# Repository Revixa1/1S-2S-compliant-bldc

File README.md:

# 1S-2S-compliant-bldc
BLDC(Brush Less DC)/PMSM(permanent magnet synchronous motor) motor supplied by 1 to 2S battery with compliance capabilities

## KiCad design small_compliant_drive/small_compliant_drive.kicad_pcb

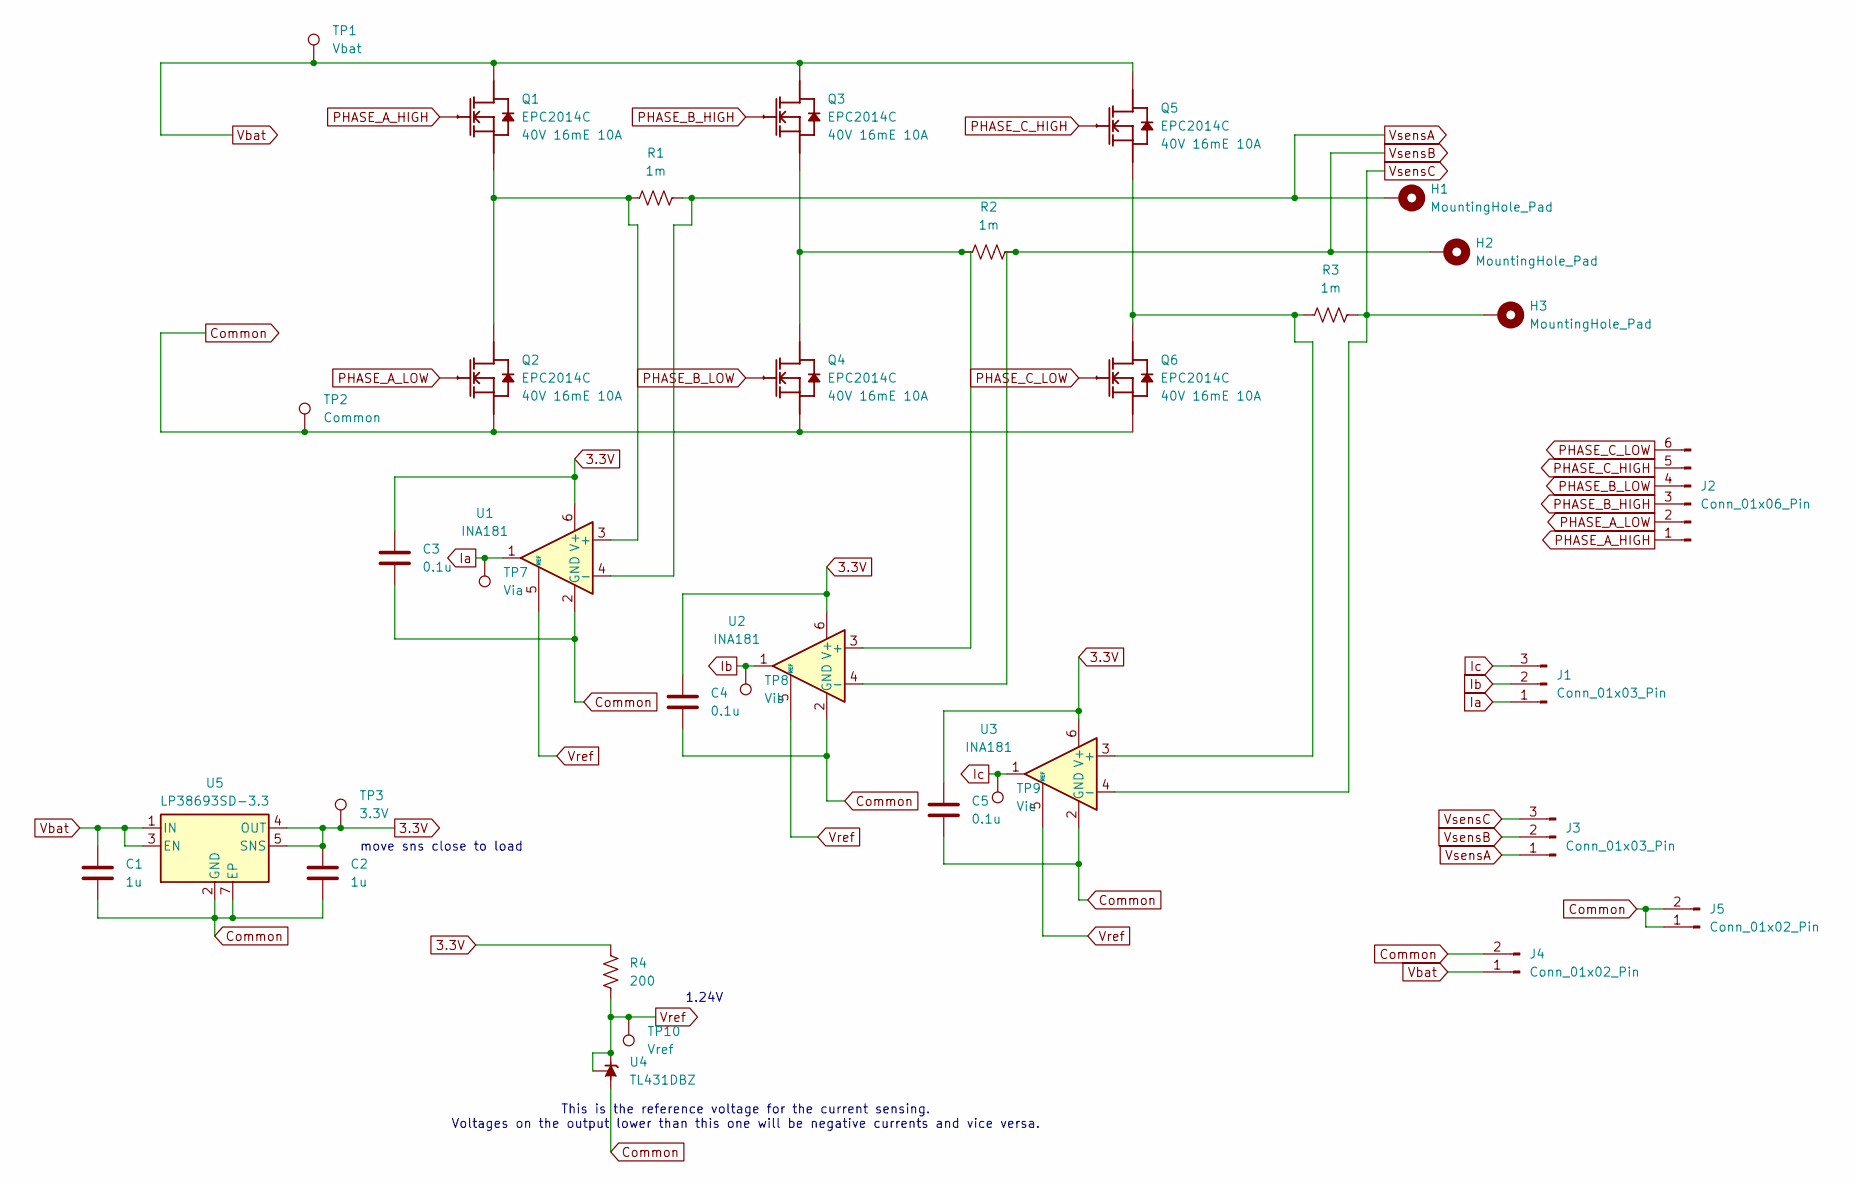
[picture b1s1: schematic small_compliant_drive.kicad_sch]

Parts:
C1, C2: 1u; C_0603_1608Metric
C3, C4, C5: 0.1u; C_0603_1608Metric
H1, H2, H3: MountingHole_Pad; MountingHole_3mm_Pad
J1, J3: Conn_01x03_Pin; PinSocket_1x03_P2.54mm_Vertical
J2: Conn_01x06_Pin; PinHeader_1x06_P2.54mm_Vertical
J4: Conn_01x02_Pin; AMASS_XT30U-M_1x02_P5.0mm_Vertical
J5: Conn_01x02_Pin; PinHeader_1x02_P2.54mm_Vertical
Q1, Q2, Q3, Q4, Q5, Q6: EPC2014C; D0199
R1, R2, R3: 1m; R_2512_6332Metric
R4: 200; R_0603_1608Metric
TP1: Vbat; TestPoint_Pad_D2.0mm
TP2: Common; TestPoint_Pad_D2.0mm
TP3: 3.3V; TestPoint_Pad_D2.0mm
TP7: Via; TestPoint_Pad_D2.0mm
TP8: Vib; TestPoint_Pad_D2.0mm
TP9: Vic; TestPoint_Pad_D2.0mm
TP10: Vref; TestPoint_Pad_D2.0mm
U1, U2, U3: INA181; SOT-23-6
U4: TL431DBZ; SOT-23
U5: LP38693SD-3.3; WSON-6-1EP_3x3mm_P0.95mm

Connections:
3.3V: C2.1, C3.1, C4.1, C5.1, R4.2, TP3.1, U1.6 (V+), U2.6 (V+), U3.6 (V+), U5.4 (OUT), U5.5 (SNS)
Common: C1.2, C2.2, C3.2, C4.2, C5.2, J4.2, J5.1, J5.2, Q2.2 (Sub), Q2.4 (S1), Q4.2 (Sub), Q4.4 (S1), Q6.2 (Sub), Q6.4 (S1), TP2.1, U1.2 (GND), U2.2 (GND), U3.2 (GND), U4.3 (A), U5.2 (GND), U5.7 (EP); also elsewhere on the board
Ia: J1.1, TP7.1, U1.1
Ib: J1.2, TP8.1, U2.1
Ic: J1.3, TP9.1, U3.1
unnamed: Q1.2 (Sub), Q1.4 (S1), Q2.3 (D1), Q2.5 (D2), R1.1, U1.3 (+)
unnamed: Q3.2 (Sub), Q3.4 (S1), Q4.3 (D1), Q4.5 (D2), R2.1, U2.3 (+)
unnamed: Q5.2 (Sub), Q5.4 (S1), Q6.3 (D1), Q6.5 (D2), R3.1, U3.3 (+)
PHASE_A_HIGH: J2.1, Q1.1 (G)
PHASE_A_LOW: J2.2, Q2.1 (G)
PHASE_B_HIGH: J2.3, Q3.1 (G)
PHASE_B_LOW: J2.4, Q4.1 (G)
PHASE_C_HIGH: J2.5, Q5.1 (G)
PHASE_C_LOW: J2.6, Q6.1 (G)
Vbat: C1.1, J4.1, Q1.3 (D1), Q1.5 (D2), Q3.3 (D1), Q3.5 (D2), Q5.3 (D1), Q5.5 (D2), TP1.1, U5.1 (IN), U5.3 (EN), U5.6 (IN); also elsewhere on the board
Vref: R4.1, TP10.1, U1.5 (REF), U2.5 (REF), U3.5 (REF), U4.1 (K), U4.2 (REF)
VsensA: H1.1, J3.1, R1.2, U1.4 (-)
VsensB: H2.1, J3.2, R2.2, U2.4 (-)
VsensC: H3.1, J3.3, R3.2, U3.4 (-)

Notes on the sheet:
1.24V
move sns close to load
This is the reference voltage for the current sensing. Voltages on the output lower than this one will be negative currents and vice versa.

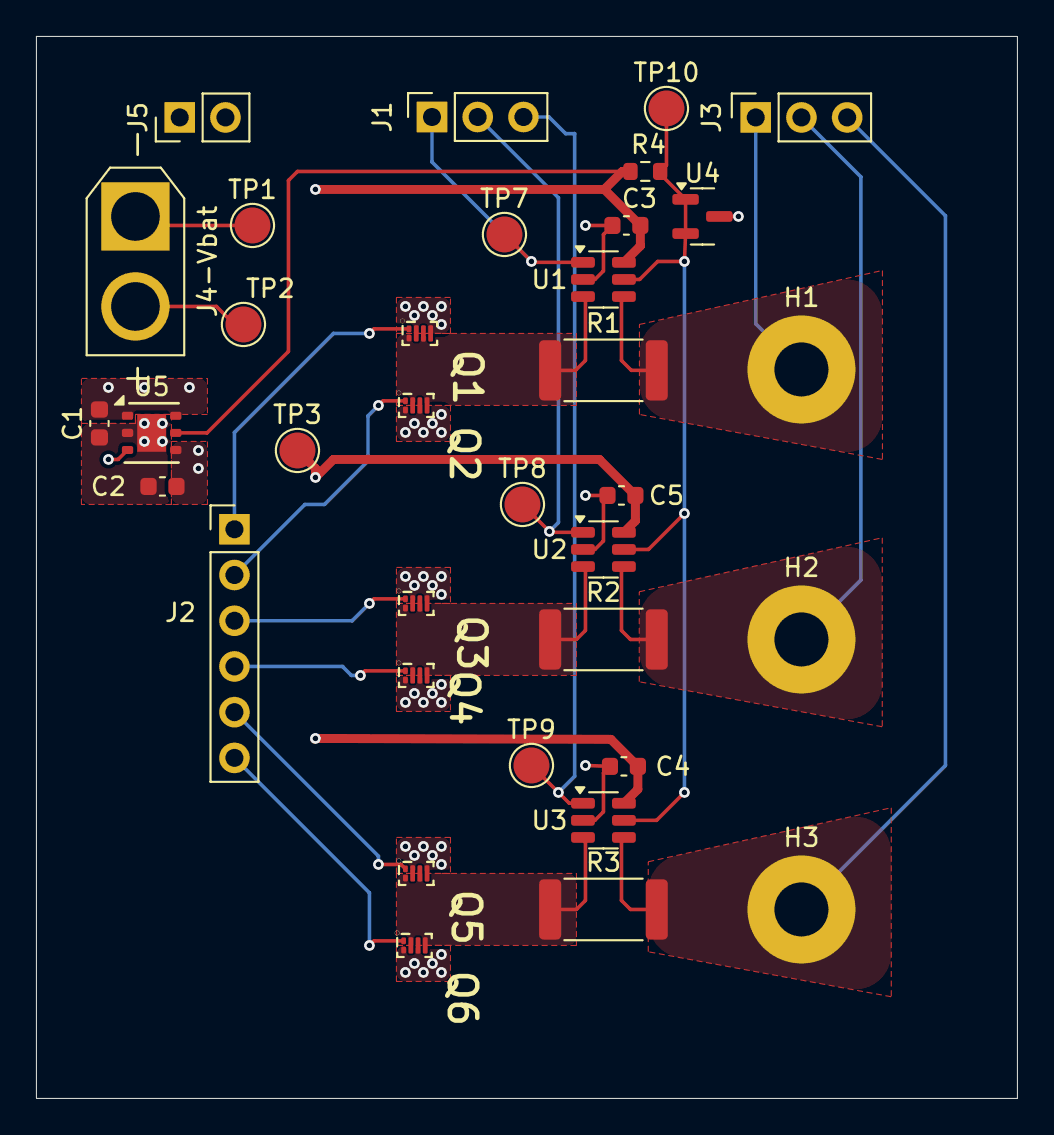
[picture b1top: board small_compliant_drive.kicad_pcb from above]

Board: 4 copper layers, 54.5 x 59.0 mm, 35 parts (0 on the bottom side), 19 nets.

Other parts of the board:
J4-Vbat: Conn_01x02_Pin; AMASS_XT30U-M_1x02_P5.0mm_Vertical

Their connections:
Common: J4-Vbat.2; also elsewhere on the board
Vbat: J4-Vbat.1; also elsewhere on the board

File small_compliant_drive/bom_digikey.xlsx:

'Reference' | 'Value' | 'Datasheet' | 'Footprint' | 'Qty' | 'DNP' | Price | Qty Factor | subTotal | qtyTotal |  | Links
'C1,C2' | '1u' | '~' | 'Capacitor_SMD:C_0603_1608Metric' | 2 | '' | 0.24099999999999999 | 10 | 4.82 | 20 |  | https://www.digikey.ca/en/products/detail/taiyo-yuden/UMK107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
'C3,C4,C5' | '0.1u' | '~' | 'Capacitor_SMD:C_0603_1608Metric' | 3 | '' | 2.12E-2 | 16.7 | 1.06212 | 50 |  | https://www.digikey.ca/en/products/detail/samsung-electro-me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
'J1,J3' | 'Conn_01x03_Pin' | '~' | 'Connector_PinSocket_2.54mm:PinSocket_1x03_P2.54mm_Vertical' | 2 | '' |  |  | 0 | 0
'J2' | 'Conn_01x06_Pin' | '~' | 'Connector_PinHeader_2.54mm:PinHeader_1x06_P2.54mm_Vertical' | 1 | '' |  |  | 0 | 0
'J4,J5' | 'Conn_01x02_Pin' | '~' | '-- valeurs mixtÃ©es --' | 2 | '' |  |  | 0 | 0
'Q1,Q2,Q3,Q4,Q5,Q6' | 'EPC2014C' | '' | 'EPC_FETs:D0199' | 6 | '' | 1.9019999999999999 | 2 | 22.823999999999998 | 12 |  | https://www.digikey.ca/en/products/detail/epc/EPC2014C/5031691
'R1,R2,R3' | '1m' | '~' | 'Resistor_SMD:R_2512_6332Metric' | 3 | '' | 0.69899999999999995 | 3.33 | 6.9830100000000002 | 10 |  | https://www.digikey.ca/en/products/detail/riedon/CSRL3-0R001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
'R4' | '200' | '~' | 'Resistor_SMD:R_0603_1608Metric' | 1 | '' | 2.9000000000000001E-2 | 10 | 0.29000000000000004 | 10 |  | https://www.digikey.ca/en/products/detail/yageo/RC0603FR-072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
'U1,U2,U3' | 'INA181' | 'http://www.ti.com/lit/ds/symlink/ina181.pdf' | 'Package_TO_SOT_SMD:SOT-23-6' | 3 | '' | 0.67 | 3.33 | 6.6933000000000007 | 10 |  | https://www.digikey.ca/en/products/detail/texas-instruments/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
'U4' | 'TL431DBZ' | 'http://www.ti.com/lit/ds/symlink/tl431.pdf' | 'Package_TO_SOT_SMD:SOT-23' | 1 | '' | 0.67 | 5 | 3.35 | 5 |  | https://www.digikey.ca/en/products/detail/taiwan-semiconduct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
'U5' | 'LP38693SD-3.3' | 'https://www.ti.com/lit/ds/symlink/lp38693.pdf' | 'Package_SON:WSON-6-1EP_3x3mm_P0.95mm' | 1 | '' | 2.68 | 5 | 13.4 | 5 |  | https://www.digikey.ca/en/products/detail/texas-instruments/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
 |  |  |  |  |  |  |  |  | 59.422429999999999 | total

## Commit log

2024-05-27 start of RevA
2024-06-03 v1 prototype done and bought
